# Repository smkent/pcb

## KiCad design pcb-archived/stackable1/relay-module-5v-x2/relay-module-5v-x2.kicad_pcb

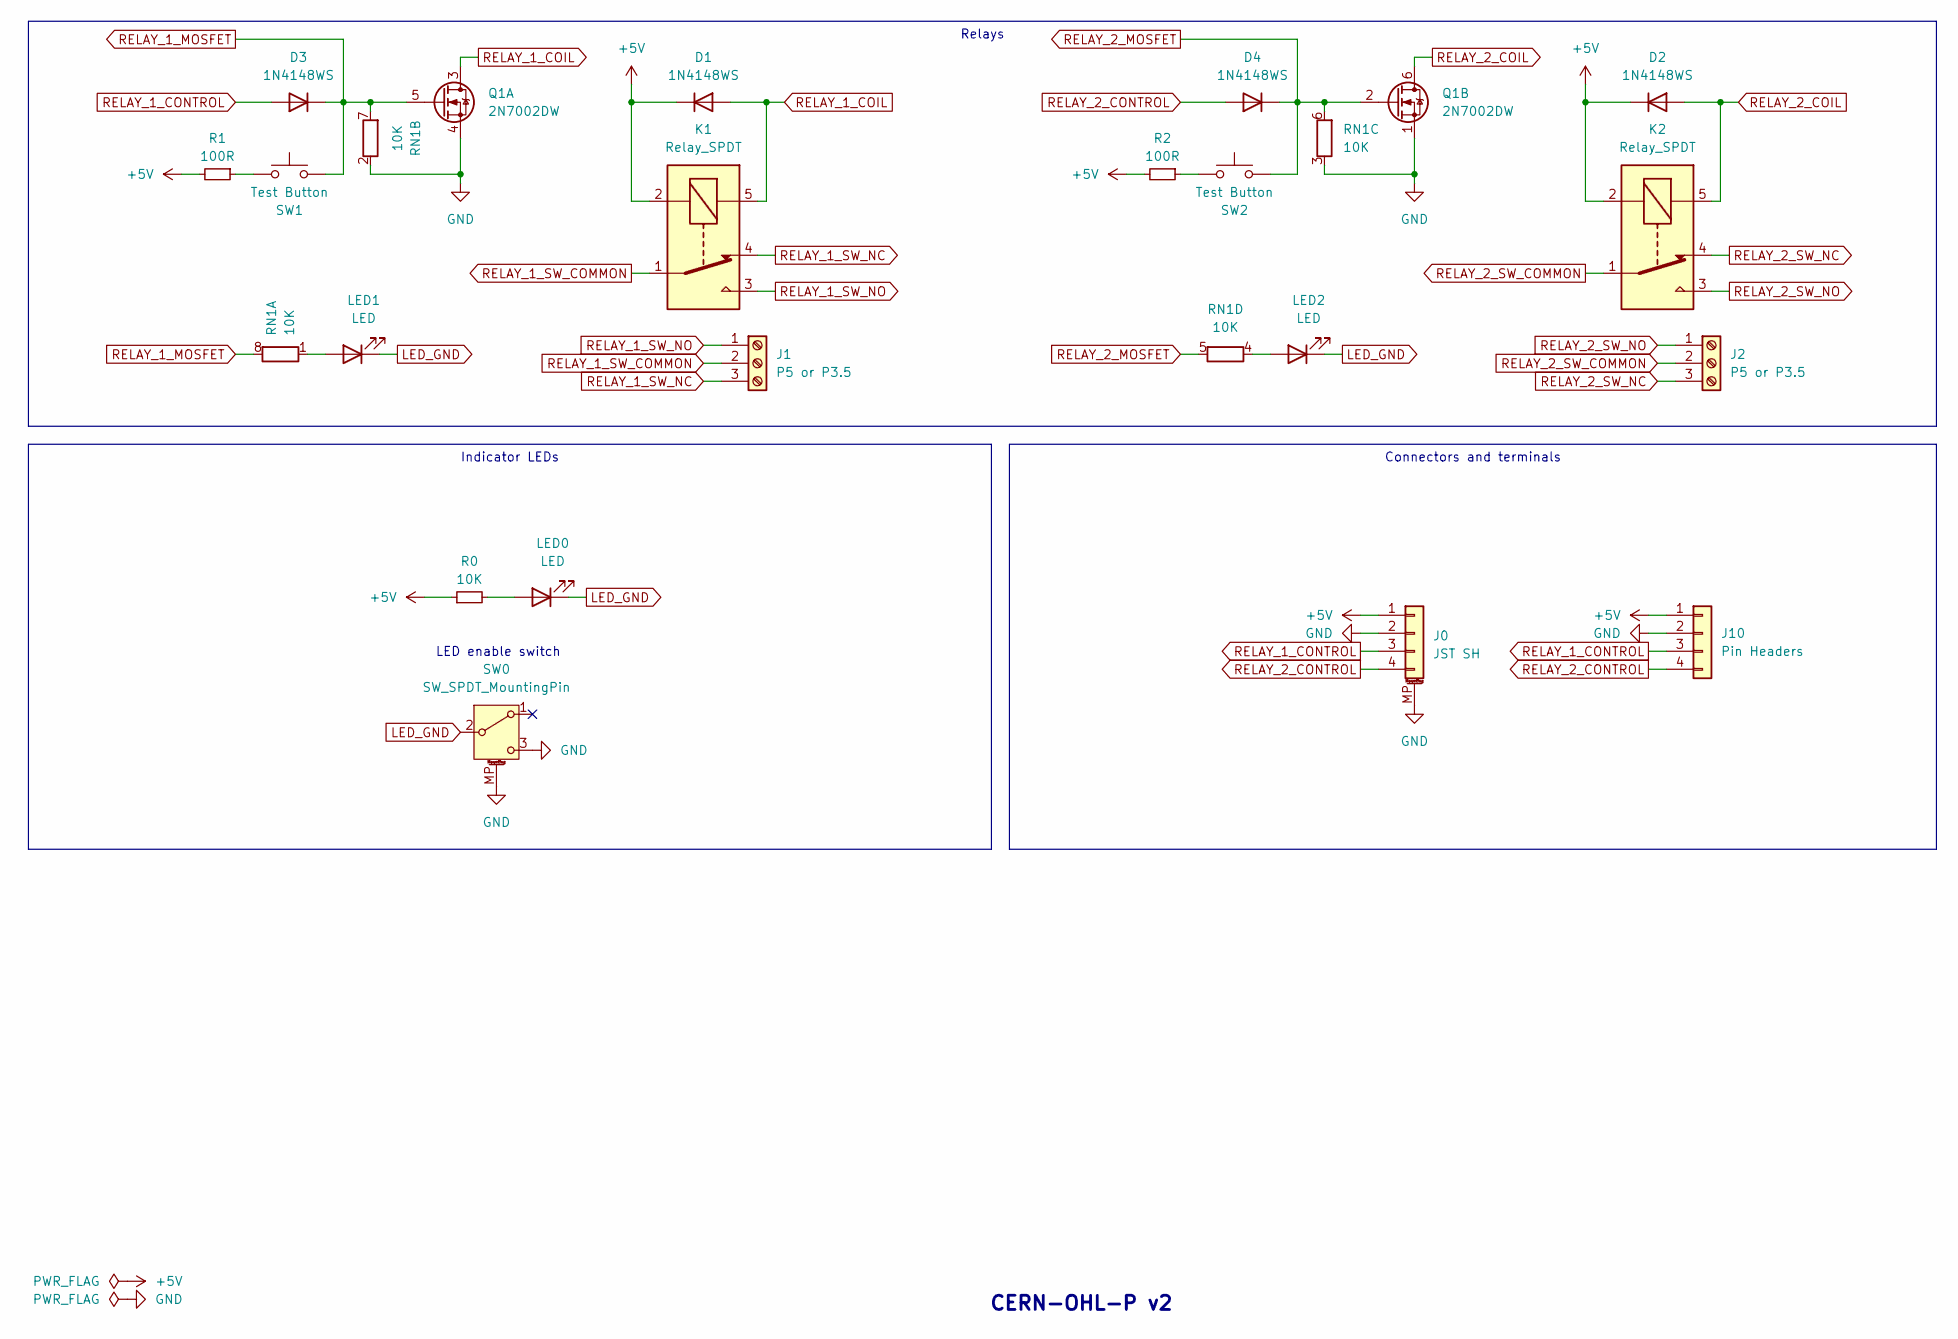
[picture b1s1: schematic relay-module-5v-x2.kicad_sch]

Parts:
D1, D2, D3, D4: 1N4148WS; D_SOD-323_HandSoldering_simple
J0: JST SH; JST_SH_SM04B-SRSS-TB_1x04-1MP_P1.00mm_Horizontal
J1, J2: P5 or P3.5; Conn_Combo_TerminalBlock_P3.5-P5.08_JST-XH_1x03
J10: Pin Headers; PinHeader_1x04_P2.54mm_Vertical_simple_pad2gnd
K1, K2: Relay_SPDT; Relay_SPDT_SANYOU_SRD_Series_Form_C
LED0, LED1, LED2: LED; LED_0805_2012Metric_Pad1.15x1.40mm_HandSolder_simple
Q1: 2N7002DW; SOT-23-6; LCSC Part C5190214
R0: 10K; R_0805_2012Metric_Pad1.20x1.40mm_HandSolder
R1, R2: 100R; R_0805_2012Metric_Pad1.20x1.40mm_HandSolder
RN1: 10K; R_Array_Convex_4x0603
SW0: SW_SPDT_MountingPin; SW-SMD_3P-P1.50_L2.7-W6.6
SW1, SW2: Test Button; SW-SMD_BZCN_TSA002A35XXX

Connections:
+5V: D1.1 (K), D2.1 (K), J0.1, J10.1, K1.2, K2.2, R0.1, R1.2, R2.2
GND: J0.2, J0.MP (MountPin), J10.2, Q1.1 (S), Q1.4 (S), RN1.2 (R2.1), RN1.3 (R3.1), SW0.3 (C), SW0.MP (MountPin)
LED_GND: LED0.1 (K), LED1.1 (K), LED2.1 (K), SW0.2 (B)
unnamed: LED0.2 (A), R0.2
unnamed: LED1.2 (A), RN1.1 (R1.1)
unnamed: LED2.2 (A), RN1.4 (R4.1)
unnamed: R1.1, SW1.2
unnamed: R2.1, SW2.2
RELAY_1_COIL: D1.2 (A), K1.5, Q1.3 (D)
RELAY_1_CONTROL: D3.2 (A), J0.3, J10.3
RELAY_1_MOSFET: D3.1 (K), Q1.5 (G), RN1.7 (R2.2), RN1.8 (R1.2), SW1.1
RELAY_1_SW_COMMON: J1.2, K1.1
RELAY_1_SW_NC: J1.3, K1.4
RELAY_1_SW_NO: J1.1, K1.3
RELAY_2_COIL: D2.2 (A), K2.5, Q1.6 (D)
RELAY_2_CONTROL: D4.2 (A), J0.4, J10.4
RELAY_2_MOSFET: D4.1 (K), Q1.2 (G), RN1.5 (R4.2), RN1.6 (R3.2), SW2.1
RELAY_2_SW_COMMON: J2.2, K2.1
RELAY_2_SW_NC: J2.3, K2.4
RELAY_2_SW_NO: J2.1, K2.3

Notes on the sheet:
Indicator LEDs
Relays
Connectors and terminals
CERN-OHL-P v2
LED enable switch

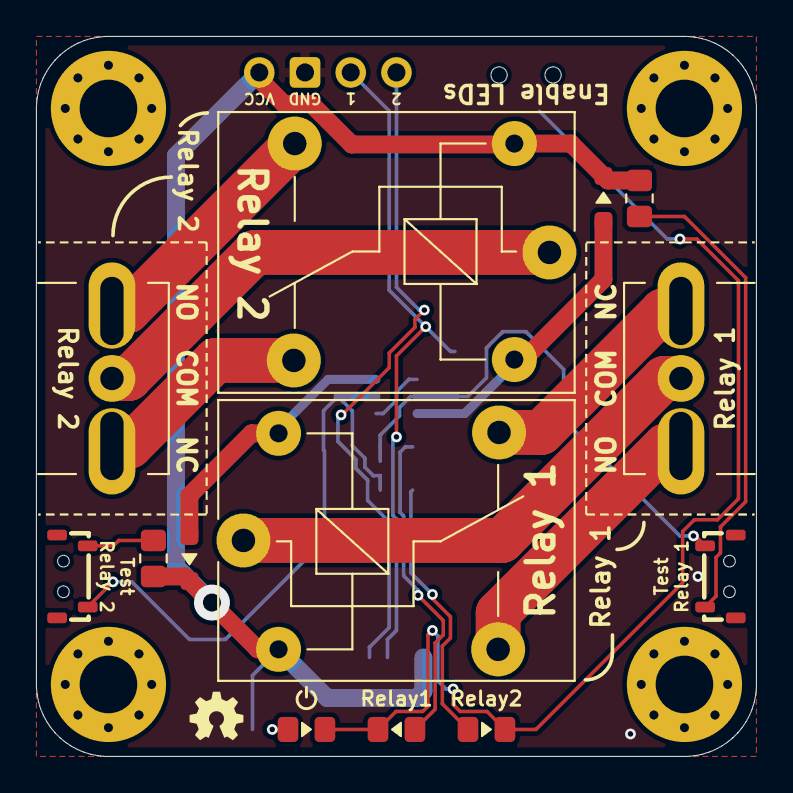
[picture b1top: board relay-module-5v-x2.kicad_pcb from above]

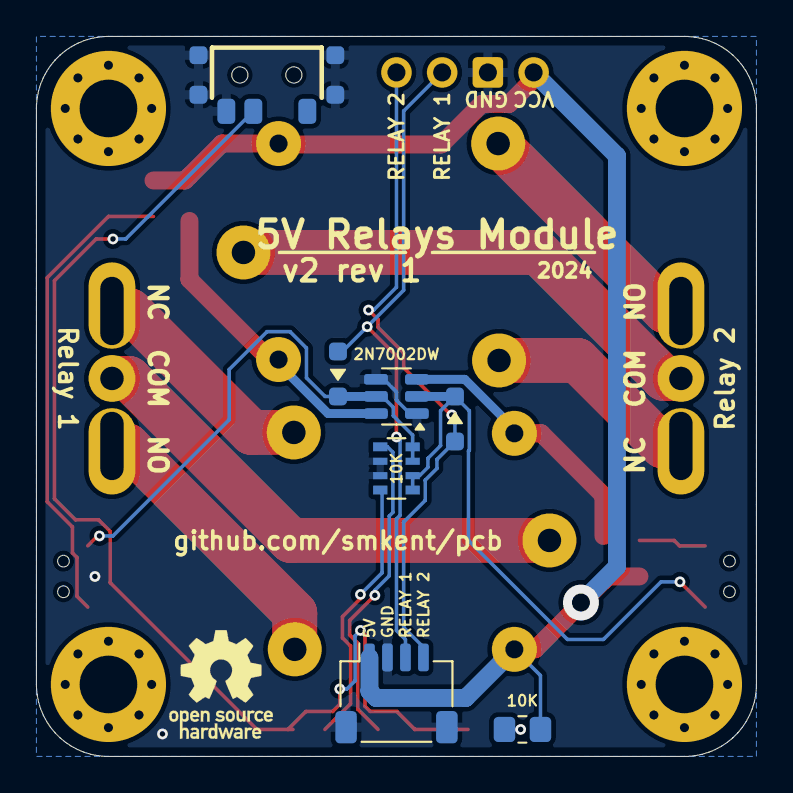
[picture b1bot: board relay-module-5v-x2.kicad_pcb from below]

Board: 2 copper layers, 40.0 x 40.0 mm, 21 parts (7 on the bottom side), 20 nets.

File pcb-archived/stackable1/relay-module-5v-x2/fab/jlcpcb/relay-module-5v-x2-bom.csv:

Comment,Designator,Footprint,LCSC
Pin Headers,J10,custom:PinHeader_1x04_P2.54mm_Vertical_simple_pad2gnd,
Relay_SPDT,"K1,K2",Relay_THT:Relay_SPDT_SANYOU_SRD_Series_Form_C,
100R,"R1,R2",Resistor_SMD:R_0805_2012Metric_Pad1.20x1.40mm_HandSolder,
10K,RN1,Resistor_SMD:R_Array_Convex_4x0603,
LED,"LED0,LED1,LED2",custom:LED_0805_2012Metric_Pad1.15x1.40mm_HandSolder_simple,
1N4148WS,"D1,D2,D3,D4",custom:D_SOD-323_HandSoldering_simple,
10K,R0,Resistor_SMD:R_0805_2012Metric_Pad1.20x1.40mm_HandSolder,
P5 or P3.5,"J1,J2",custom:Conn_Combo_TerminalBlock_P3.5-P5.08_JST-XH_1x03,
2N7002DW,Q1,Package_TO_SOT_SMD:SOT-23-6,C5190214
JST SH,J0,connectors:JST_SH_SM04B-SRSS-TB_1x04-1MP_P1.00mm_Horizontal,
Test Button,"SW1,SW2",lcsc:SW-SMD_BZCN_TSA002A35XXX,
SW_SPDT_MountingPin,SW0,lcsc:SW-SMD_3P-P1.50_L2.7-W6.6,

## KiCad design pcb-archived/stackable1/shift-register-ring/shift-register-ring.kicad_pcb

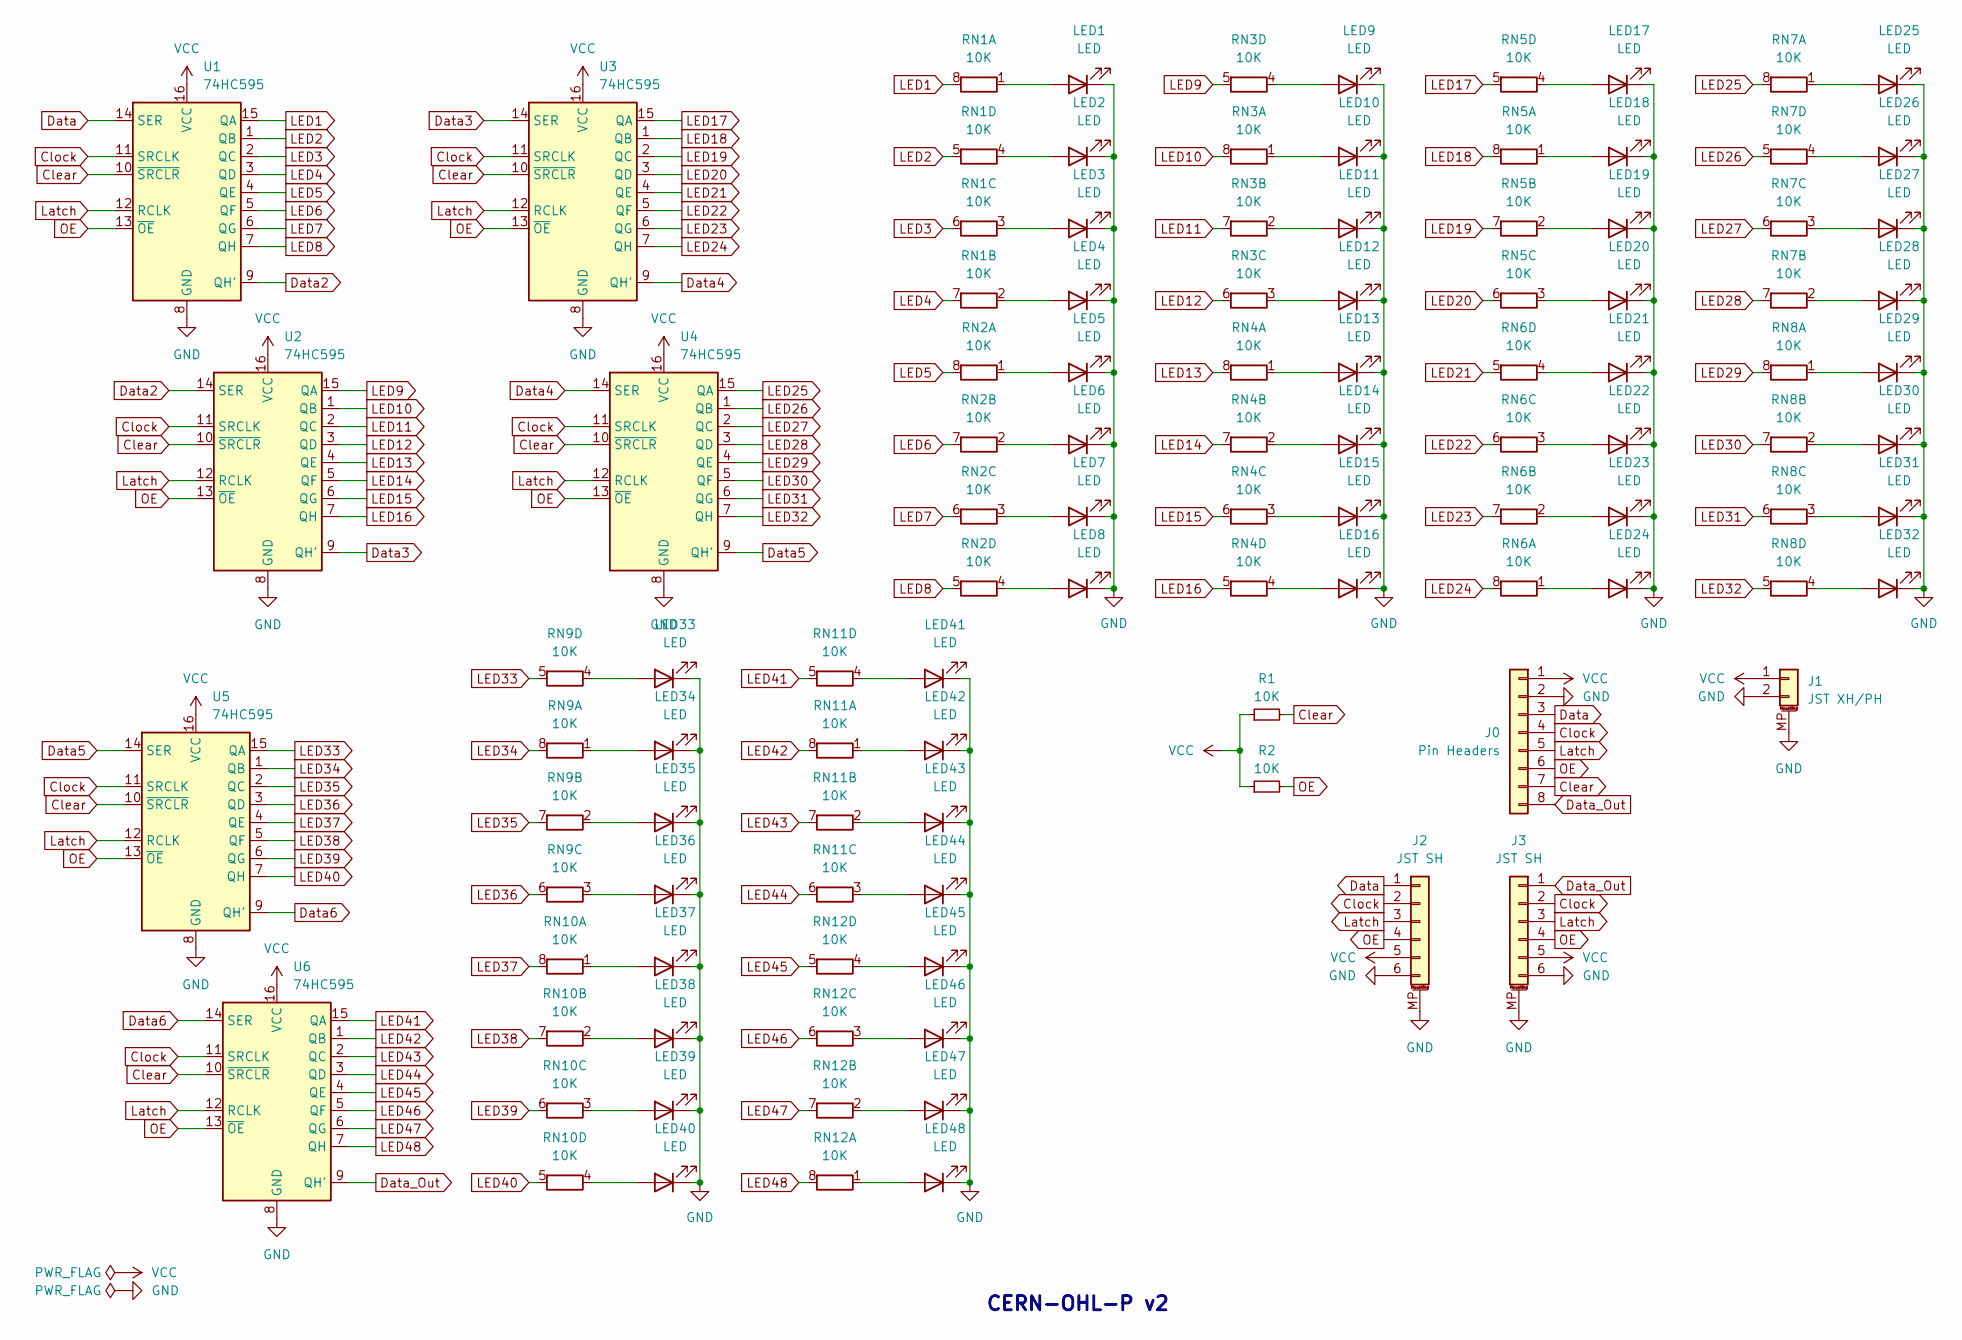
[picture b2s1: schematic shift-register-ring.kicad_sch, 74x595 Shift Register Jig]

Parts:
J0: Pin Headers; PinHeader_1x08_P2.54mm_Vertical_simple_pad2gnd
J1: JST XH/PH; Conn_Combo_JST-1x02-XH_PH-SMD-pad2gnd
J2, J3: JST SH; JST_SH_SM06B-SRSS-TB_1x06-1MP_P1.00mm_Horizontal
LED1, LED2, LED3, LED4, LED5, LED6, LED7, LED8, LED9, LED10, LED11, LED12, LED13, LED14, LED15, LED16, LED17, LED18, LED19, LED20, LED21, LED22, LED23, LED24, LED25, LED26, LED27, LED28, LED29, LED30, LED31, LED32, LED33, LED34, LED35, LED36, LED37, LED38, LED39, LED40, LED41, LED42, LED43, LED44, LED45, LED46, LED47, LED48: LED; LED_0603_1608Metric_Pad1.05x0.95mm_HandSolder_simple
R1, R2: 10K; R_0603_1608Metric_Pad0.98x0.95mm_HandSolder
RN1, RN2, RN3, RN4, RN5, RN6, RN7, RN8, RN9, RN10, RN11, RN12: 10K; R_Array_Convex_4x0603
U1, U2, U3, U4, U5, U6: 74HC595; SOIC-16_3.9x9.9mm_P1.27mm

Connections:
Clear: J0.7, R1.2, U1.10 (~SRCLR), U2.10 (~SRCLR), U3.10 (~SRCLR), U4.10 (~SRCLR), U5.10 (~SRCLR), U6.10 (~SRCLR)
Clock: J0.4, J2.2, J3.2, U1.11 (SRCLK), U2.11 (SRCLK), U3.11 (SRCLK), U4.11 (SRCLK), U5.11 (SRCLK), U6.11 (SRCLK)
Data: J0.3, J2.1, U1.14 (SER)
Data2: U1.9 (QH'), U2.14 (SER)
Data3: U2.9 (QH'), U3.14 (SER)
Data4: U3.9 (QH'), U4.14 (SER)
Data5: U4.9 (QH'), U5.14 (SER)
Data6: U5.9 (QH'), U6.14 (SER)
Data_Out: J0.8, J3.1, U6.9 (QH')
GND: J0.2, J1.2, J1.MP (MountPin), J2.6, J2.MP (MountPin), J3.6, J3.MP (MountPin), LED1.1 (K), LED2.1 (K), LED3.1 (K), LED4.1 (K), LED5.1 (K), LED6.1 (K), LED7.1 (K), LED8.1 (K), LED9.1 (K), LED10.1 (K), LED11.1 (K), LED12.1 (K), LED13.1 (K), LED14.1 (K), LED15.1 (K), LED16.1 (K), LED17.1 (K), LED18.1 (K), LED19.1 (K), LED20.1 (K), LED21.1 (K), LED22.1 (K), LED23.1 (K), LED24.1 (K), LED25.1 (K), LED26.1 (K), LED27.1 (K), LED28.1 (K), LED29.1 (K), LED30.1 (K), LED31.1 (K), LED32.1 (K), LED33.1 (K), LED34.1 (K), LED35.1 (K), LED36.1 (K), LED37.1 (K), LED38.1 (K), LED39.1 (K), LED40.1 (K), LED41.1 (K), LED42.1 (K), LED43.1 (K), LED44.1 (K), LED45.1 (K), LED46.1 (K), LED47.1 (K), LED48.1 (K), U1.8 (GND), U2.8 (GND), U3.8 (GND), U4.8 (GND), U5.8 (GND), U6.8 (GND)
LED1: RN1.8 (R1.2), U1.15 (QA)
LED2: RN1.5 (R4.2), U1.1 (QB)
LED3: RN1.6 (R3.2), U1.2 (QC)
LED4: RN1.7 (R2.2), U1.3 (QD)
LED5: RN2.8 (R1.2), U1.4 (QE)
LED6: RN2.7 (R2.2), U1.5 (QF)
LED7: RN2.6 (R3.2), U1.6 (QG)
LED8: RN2.5 (R4.2), U1.7 (QH)
LED9: RN3.5 (R4.2), U2.15 (QA)
LED10: RN3.8 (R1.2), U2.1 (QB)
LED11: RN3.7 (R2.2), U2.2 (QC)
LED12: RN3.6 (R3.2), U2.3 (QD)
LED13: RN4.8 (R1.2), U2.4 (QE)
LED14: RN4.7 (R2.2), U2.5 (QF)
LED15: RN4.6 (R3.2), U2.6 (QG)
LED16: RN4.5 (R4.2), U2.7 (QH)
LED17: RN5.5 (R4.2), U3.15 (QA)
LED18: RN5.8 (R1.2), U3.1 (QB)
LED19: RN5.7 (R2.2), U3.2 (QC)
LED20: RN5.6 (R3.2), U3.3 (QD)
LED21: RN6.5 (R4.2), U3.4 (QE)
LED22: RN6.6 (R3.2), U3.5 (QF)
LED23: RN6.7 (R2.2), U3.6 (QG)
LED24: RN6.8 (R1.2), U3.7 (QH)
LED25: RN7.8 (R1.2), U4.15 (QA)
LED26: RN7.5 (R4.2), U4.1 (QB)
LED27: RN7.6 (R3.2), U4.2 (QC)
LED28: RN7.7 (R2.2), U4.3 (QD)
LED29: RN8.8 (R1.2), U4.4 (QE)
LED30: RN8.7 (R2.2), U4.5 (QF)
LED31: RN8.6 (R3.2), U4.6 (QG)
LED32: RN8.5 (R4.2), U4.7 (QH)
LED33: RN9.5 (R4.2), U5.15 (QA)
LED34: RN9.8 (R1.2), U5.1 (QB)
LED35: RN9.7 (R2.2), U5.2 (QC)
LED36: RN9.6 (R3.2), U5.3 (QD)
LED37: RN10.8 (R1.2), U5.4 (QE)
LED38: RN10.7 (R2.2), U5.5 (QF)
LED39: RN10.6 (R3.2), U5.6 (QG)
LED40: RN10.5 (R4.2), U5.7 (QH)
LED41: RN11.5 (R4.2), U6.15 (QA)
LED42: RN11.8 (R1.2), U6.1 (QB)
LED43: RN11.7 (R2.2), U6.2 (QC)
LED44: RN11.6 (R3.2), U6.3 (QD)
LED45: RN12.5 (R4.2), U6.4 (QE)
LED46: RN12.6 (R3.2), U6.5 (QF)
LED47: RN12.7 (R2.2), U6.6 (QG)
LED48: RN12.8 (R1.2), U6.7 (QH)
Latch: J0.5, J2.3, J3.3, U1.12 (RCLK), U2.12 (RCLK), U3.12 (RCLK), U4.12 (RCLK), U5.12 (RCLK), U6.12 (RCLK)
unnamed: LED1.2 (A), RN1.1 (R1.1)
unnamed: LED2.2 (A), RN1.4 (R4.1)
unnamed: LED3.2 (A), RN1.3 (R3.1)
unnamed: LED4.2 (A), RN1.2 (R2.1)
unnamed: LED5.2 (A), RN2.1 (R1.1)
unnamed: LED6.2 (A), RN2.2 (R2.1)
unnamed: LED7.2 (A), RN2.3 (R3.1)
unnamed: LED8.2 (A), RN2.4 (R4.1)
unnamed: LED9.2 (A), RN3.4 (R4.1)
unnamed: LED10.2 (A), RN3.1 (R1.1)
unnamed: LED11.2 (A), RN3.2 (R2.1)
unnamed: LED12.2 (A), RN3.3 (R3.1)
unnamed: LED13.2 (A), RN4.1 (R1.1)
unnamed: LED14.2 (A), RN4.2 (R2.1)
unnamed: LED15.2 (A), RN4.3 (R3.1)
unnamed: LED16.2 (A), RN4.4 (R4.1)
unnamed: LED17.2 (A), RN5.4 (R4.1)
unnamed: LED18.2 (A), RN5.1 (R1.1)
unnamed: LED19.2 (A), RN5.2 (R2.1)
unnamed: LED20.2 (A), RN5.3 (R3.1)
unnamed: LED21.2 (A), RN6.4 (R4.1)
unnamed: LED22.2 (A), RN6.3 (R3.1)
unnamed: LED23.2 (A), RN6.2 (R2.1)
unnamed: LED24.2 (A), RN6.1 (R1.1)
unnamed: LED25.2 (A), RN7.1 (R1.1)
unnamed: LED26.2 (A), RN7.4 (R4.1)
unnamed: LED27.2 (A), RN7.3 (R3.1)
unnamed: LED28.2 (A), RN7.2 (R2.1)
unnamed: LED29.2 (A), RN8.1 (R1.1)
unnamed: LED30.2 (A), RN8.2 (R2.1)
unnamed: LED31.2 (A), RN8.3 (R3.1)
unnamed: LED32.2 (A), RN8.4 (R4.1)
unnamed: LED33.2 (A), RN9.4 (R4.1)
unnamed: LED34.2 (A), RN9.1 (R1.1)
unnamed: LED35.2 (A), RN9.2 (R2.1)
unnamed: LED36.2 (A), RN9.3 (R3.1)
unnamed: LED37.2 (A), RN10.1 (R1.1)
unnamed: LED38.2 (A), RN10.2 (R2.1)
unnamed: LED39.2 (A), RN10.3 (R3.1)
unnamed: LED40.2 (A), RN10.4 (R4.1)
unnamed: LED41.2 (A), RN11.4 (R4.1)
unnamed: LED42.2 (A), RN11.1 (R1.1)
unnamed: LED43.2 (A), RN11.2 (R2.1)
unnamed: LED44.2 (A), RN11.3 (R3.1)
unnamed: LED45.2 (A), RN12.4 (R4.1)
unnamed: LED46.2 (A), RN12.3 (R3.1)
unnamed: LED47.2 (A), RN12.2 (R2.1)
unnamed: LED48.2 (A), RN12.1 (R1.1)
OE: J0.6, J2.4, J3.4, R2.2, U1.13 (~OE), U2.13 (~OE), U3.13 (~OE), U4.13 (~OE), U5.13 (~OE), U6.13 (~OE)
VCC: J0.1, J1.1, J2.5, J3.5, R1.1, R2.1, U1.16 (VCC), U2.16 (VCC), U3.16 (VCC), U4.16 (VCC), U5.16 (VCC), U6.16 (VCC)

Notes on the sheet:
CERN-OHL-P v2

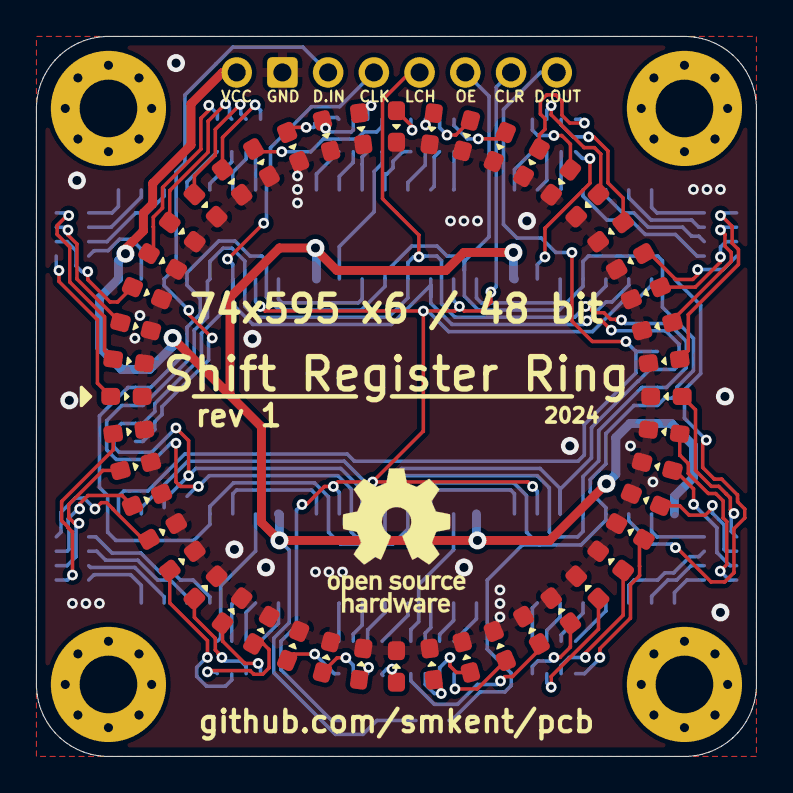
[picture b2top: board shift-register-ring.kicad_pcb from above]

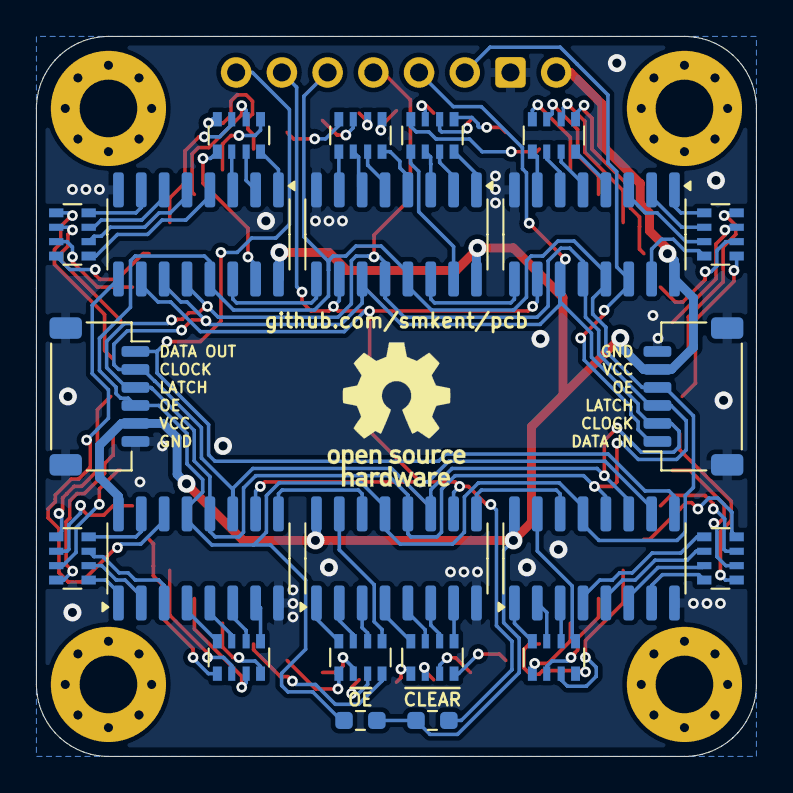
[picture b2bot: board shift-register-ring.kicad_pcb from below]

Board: 2 copper layers, 40.0 x 40.0 mm, 71 parts (23 on the bottom side), 109 nets.

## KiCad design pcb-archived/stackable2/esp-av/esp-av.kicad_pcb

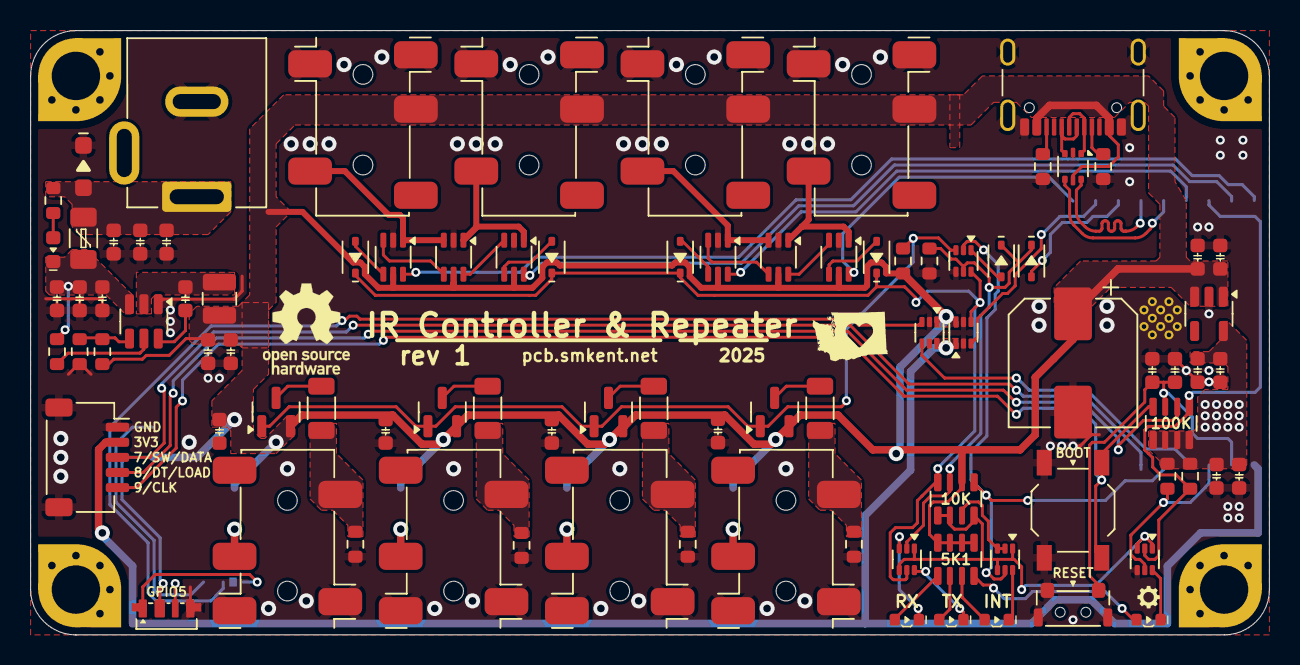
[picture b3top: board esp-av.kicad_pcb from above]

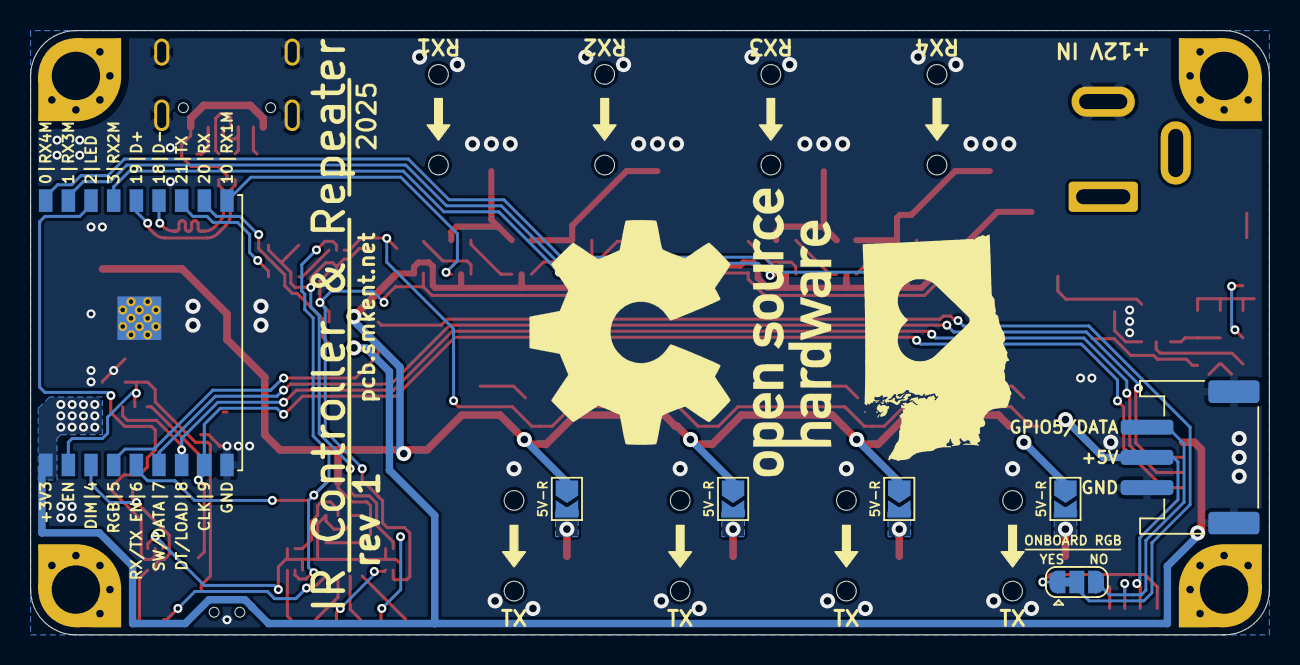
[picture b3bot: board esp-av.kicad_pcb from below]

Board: 2 copper layers, 82.0 x 40.0 mm, 97 parts (7 on the bottom side), 71 nets.

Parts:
C1, C4, C5, C10, C11: 10u; C_0603_1608Metric
C2, C3, C6, C8, C12, C13: 0u1; C_0603_1608Metric
C7: 1u; C_0603_1608Metric
C9: 1000u; CP_Elec_8x10
C14, C15, C16, C17, C18, C19, C20, C21, C22: 22u; C_0603_1608Metric
D0: D_TVS; D_SOD-123F
D1, D2, D3, D4, D5, D6: 1N4148WS; D_SOD-323
F1: 16V 2A; Fuse_1206_3216Metric
J0: DC-005; BarrelJack_DC-005_THT_Horizontal
J1: USB_C_Receptacle_USB2.0_16P; USB_C_Receptacle_GCT_USB4105-xx-A_16P_TopMnt_Horizontal
J2, J3, J4, J5, J6, J7, J8, J9: PJ-327U; Jack_3.5mm_PJ-327U-SMT_Horizontal
J10: JST SH; JST_SH_SM05B-SRSS-TB_1x05-1MP_P1.00mm_Horizontal
J11: STEMMA-Signal; STEMMA-Signal-SMD-horizontal
JP1, JP2, JP3, JP4: Open; SolderJumper-2_P1.3mm_Open_TrianglePad1.0x1.5mm
JP5: 1-2; SolderJumper-3_P1.3mm_Bridged12_RoundedPad1.0x1.5mm
L1: 4u7; L_1008_2520Metric
LED0: Red; LED_0603_1608Metric
LED1, LED2: XL-1606UWC; LED_SideEmitter_1.7x1.1mm
LED3, LED4: XL-1606UBC; LED_SideEmitter_1.7x1.1mm
LED5: SK6812SIDE-A; LED_SK6812SIDE-A_4.0x1.6mm
Q1, Q7, Q8, Q9: PDNM6ET20V05; SOT-563
Q3, Q4, Q5, Q6: AO3401A; SOT-23
R1, R2: 5K1; R_0603_1608Metric
R3, R4, R9: 10K; R_0603_1608Metric
R5, R6, R7, R16, R17, R18: 100K; R_0603_1608Metric
R8: 57K6; R_0603_1608Metric
R10, R11: 2K2; R_0603_1608Metric
R12, R13, R14, R15: 15R; R_1206_3216Metric
RN1: 5K1; R_Array_Convex_4x0603_HandSolder
RN2: 10K; R_Array_Convex_4x0603_HandSolder
RN3: 100K; R_Array_Convex_4x0603_HandSolder
SM1: ESP32-C3-WROOM-02
SW1: Reset; SW_Push_1P1T-MP_NO_4.6x3mm_Horizontal
SW2: Boot; SW_SPST_TL3342
U1: USBLC6-2P6; SOT-666
U2: ME6211C33M5; SOT-23-5
U3: TPS563201; SOT-23-6
U4, U5: NC7WZ14P6X; SOT-363_SC-70-6_HandSolder
U6, U7, U8, U9: SN74LVC1G157DC; SOT-363_SC-70-6_HandSolder
U10, U11: SN74LVC1T45Z6; SOT-563

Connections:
+3V3: C3.1, C4.1, C5.1, C6.1, J10.2, R16.2, R18.2, RN3.5 (R4.2), RN3.6 (R3.2), RN3.7 (R2.2), RN3.8 (R1.2), SM1.1 (3V3), U2.5 (V_{OUT}), U10.1 (VCCA), U11.6 (VCCB)
+5V: C1.1, C2.1, C9.1, C14.1, C15.1, C19.1, C20.1, C21.1, C22.1, J1.A4 (VBUS), J1.A9 (VBUS), J1.B4 (VBUS), J1.B9 (VBUS), J2.R, J3.R, J4.R, J5.R, J11.2 (V+), JP1.1 (A), JP2.1 (A), JP3.1 (A), JP4.1 (A), L1.2, LED5.2 (VDD), Q3.2 (S), Q4.2 (S), Q5.2 (S), Q6.2 (S), R8.2, R11.1, RN1.5 (R4.2), RN1.6 (R3.2), RN1.7 (R2.2), RN1.8 (R1.2), RN2.6 (R3.2), U1.5 (VBUS), U2.1 (V_{IN}), U2.3 (CE), U4.5 (V_{CC}), U5.5 (V_{CC}), U6.5 (V_{CC}), U7.5 (V_{CC}), U8.5 (V_{CC}), U9.5 (V_{CC}), U10.6 (VCCB), U11.1 (VCCA)
+12V: C10.1, C11.1, C12.1, F1.2, LED0.1 (K), R3.1, U3.3 (VIN)
/CC1: J1.A5 (CC1), R2.2
/CC2: J1.B5 (CC2), R1.2
/DC_IN_RAW: C16.1, C17.1, C18.1, D0.2 (A2), F1.1, J0.1, R4.2
/Infrared Transmitter/TX1_5V_J: J6.R, JP1.2 (B)
/Infrared Transmitter/TX1_A_P: Q3.3 (D), R14.1
/Infrared Transmitter/TX2_5V_J: J7.R, JP2.2 (B)
/Infrared Transmitter/TX2_A_P: Q4.3 (D), R12.1
/Infrared Transmitter/TX3_5V_J: J8.R, JP3.2 (B)
/Infrared Transmitter/TX3_A_P: Q5.3 (D), R15.1
/Infrared Transmitter/TX4_5V_J: J9.R, JP4.2 (B)
/Infrared Transmitter/TX4_A_P: Q6.3 (D), R13.1
/PIXEL_DATA: JP5.2 (C), U11.3 (A)
/PIXEL_DIN: JP5.1 (A), LED5.1 (DIN)
/RX_5V_SW: D2.2 (A), Q1.1 (S)
/SW_5V: C13.2, L1.1, U3.2 (SW)
/USB_DM: J1.A7 (D-), J1.B7 (D-), U1.1 (I/O1)
/USB_DP: J1.A6 (D+), J1.B6 (D+), U1.3 (I/O2)
D+: SM1.14 (IO19/USB_D+), U1.4 (I/O2)
D-: SM1.13 (IO18/USB_D-), U1.6 (I/O1)
ESP32_EN: C7.1, C8.1, RN3.3 (R3.1), SM1.2 (EN), SW1.1
FB_5V: R8.1, R9.2, U3.4 (VFB)
GND: C1.2, C2.2, C3.2, C4.2, C5.2, C6.2, C7.2, C8.2, C9.2, C10.2, C11.2, C12.2, C14.2, C15.2, C16.2, C17.2, C18.2, C19.2, C20.2, C21.2, C22.2, D0.1 (A1), J0.2, J1.A1 (GND), J1.A12 (GND), J1.B1 (GND), J1.B12 (GND), J1.S1 (SHIELD), J2.S, J3.S, J4.S, J5.S, J6.S, J7.S, J8.S, J9.S, J10.1, J10.MP (MountPin), J11.1 (Sig), J11.MP, LED5.4 (VSS), Q1.4 (S), Q9.4 (S), R1.1, R2.1, R5.2, R6.2, R7.2, R9.1, R10.2, R17.2, SM1.9 (GND), SM1.19 (GND), SW1.2, SW1.MP (MountPin), SW2.2, U1.2 (GND), U2.2 (V_{SS}), U3.1 (GND), U4.2 (GND), U5.2 (GND), U6.2 (GND), U7.2 (GND), U8.2 (GND), U9.2 (GND), U10.2 (GND), U10.5 (DIR), U11.2 (GND), U11.5 (DIR)
GPIO2: Q9.2 (G), R16.1, RN3.1 (R1.1), SM1.16 (IO2)
IO7/SW/DATA: J10.3, SM1.6 (IO7)
IO8/DT/LOAD: J10.4, RN3.2 (R2.1), SM1.7 (IO8)
IO9/CLK: J10.5, RN3.4 (R4.1), SM1.8 (IO9), SW2.1
LED_EN: Q9.5 (G), R18.1, SM1.3 (IO4)
LED_GND: Q7.1 (S), Q7.4 (S), Q8.1 (S), Q8.4 (S), Q9.1 (S), Q9.3 (D), RN2.1 (R1.1), RN2.2 (R2.1), RN2.4 (R4.1)
unnamed: D3.2 (A), U6.4 (Y)
unnamed: D4.2 (A), U7.4 (Y)
unnamed: D5.2 (A), U8.4 (Y)
unnamed: D6.2 (A), U9.4 (Y)
unnamed: LED0.2 (A), R4.1
unnamed: LED1.2 (A), RN1.4 (R4.1)
unnamed: LED1.1 (K), Q9.6 (D)
unnamed: LED2.2 (A), RN1.3 (R3.1)
unnamed: LED2.1 (K), Q8.6 (D)
unnamed: LED3.2 (A), RN1.1 (R1.1)
unnamed: LED3.1 (K), Q7.3 (D)
unnamed: LED4.2 (A), RN1.2 (R2.1)
unnamed: LED4.1 (K), Q7.6 (D)
unnamed: Q8.2 (G), Q8.3 (D), RN2.3 (R3.1)
unnamed: R3.2, U3.5 (EN)
unnamed: C13.1, U3.6 (VBST)
PIXEL_DATA_3V3: SM1.4 (IO5), U11.4 (B)
PIXEL_DOUT: J11.3 (GND), JP5.3 (B), LED5.3 (DOUT)
RX: D3.1 (K), D4.1 (K), D5.1 (K), D6.1 (K), Q1.6 (D), Q7.5 (G), RN2.8 (R1.2), U10.4 (B)
RX1_5V: J2.T, U4.1 (1A), U6.1 (I1)
RX1_5V_INV: U4.6 (1Y), U6.3 (I0)
RX1_MODE: SM1.10 (IO10), U6.6 (S)
RX2_5V: J3.T, U4.3 (2A), U7.1 (I1)
RX2_5V_INV: U4.4 (2Y), U7.3 (I0)
RX2_MODE: SM1.15 (IO3), U7.6 (S)
RX3_5V: J4.T, U5.1 (1A), U8.1 (I1)
RX3_5V_INV: U5.6 (1Y), U8.3 (I0)
RX3_MODE: SM1.17 (IO1), U8.6 (S)
RX4_5V: J5.T, U5.3 (2A), U9.1 (I1)
RX4_5V_INV: U5.4 (2Y), U9.3 (I0)
RX4_MODE: SM1.18 (IO0), U9.6 (S)
RX_3V3: SM1.11 (IO20/RXD), U10.3 (A)
RX_TX_EN: Q1.2 (G), Q8.5 (G), RN2.5 (R4.2), SM1.5 (IO6)
TX: D1.1 (K), D2.1 (K), Q1.5 (G), Q7.2 (G), R10.1, RN2.7 (R2.2)
TX1_A: J6.T, R5.1, R14.2
TX2_A: J7.T, R6.1, R12.2
TX3_A: J8.T, R7.1, R15.2
TX4_A: J9.T, R13.2, R17.1
TX_3V3: D1.2 (A), SM1.12 (IO21/TXD)
TX_INV: Q1.3 (D), Q3.1 (G), Q4.1 (G), Q5.1 (G), Q6.1 (G), R11.2

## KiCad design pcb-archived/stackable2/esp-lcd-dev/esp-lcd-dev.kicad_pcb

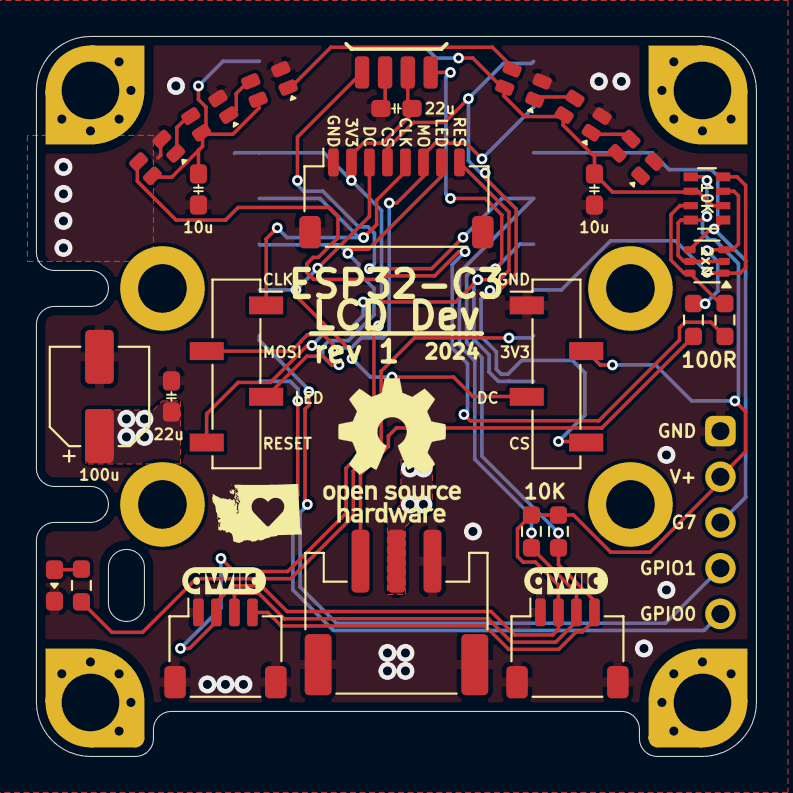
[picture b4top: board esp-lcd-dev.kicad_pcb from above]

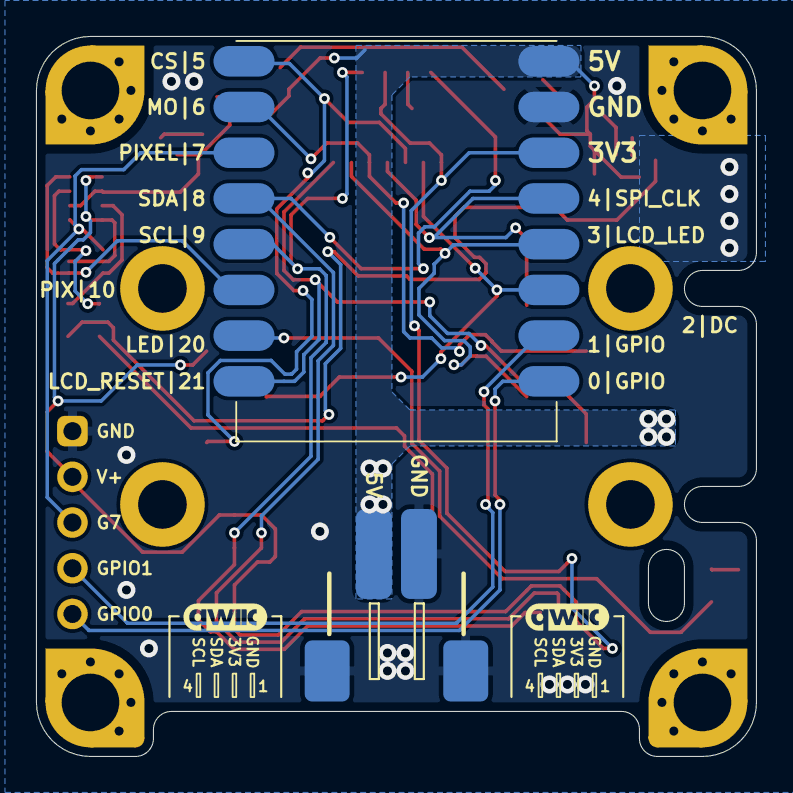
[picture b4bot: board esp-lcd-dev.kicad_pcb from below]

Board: 2 copper layers, 40.0 x 40.0 mm, 29 parts (3 on the bottom side), 26 nets.

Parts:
C1: 100u; CP_Elec_5x5.4
C2, C3: 22u; C_0603_1608Metric_Pad1.08x0.95mm_HandSolder
C6, C7: 10u; C_0603_1608Metric_Pad1.08x0.95mm_HandSolder
J1: JST XH/PH; Conn_Combo_JST-1x02-XH_PH-SMD-pad2gnd
J2, J3: Qwiic; Qwiic-SMD-horizontal-logo-bottom-pinout
J4: STEMMA-Signal; STEMMA-Signal-SMD-horizontal
J5: JST SH; JST_SH_SM08B-SRSS-TB_1x08-1MP_P1.00mm_Horizontal
J6: Pin headers; PinHeader_1x05_P2.54mm_Vertical_simple_pad1gnd
J7: Pin headers; PinSocket_1x04_P2.54mm_Vertical_SMD_Pin1Right
J8: Pin headers; PinSocket_1x04_P2.54mm_Vertical_SMD_Pin1Left
LED1: LED_Small; LED_0603_1608Metric_Pad1.05x0.95mm_HandSolder_simple
LED2, LED3, LED4, LED5, LED6, LED7: WS2812B-2020; LED_WS2812B-2020_PLCC4_2.0x2.0mm_HandSolder
Q1: 2N7002DW; SOT-363_SC-70-6
R1, R4, R5: 10K; R_0603_1608Metric_Pad0.98x0.95mm_HandSolder
R2, R3: 100R; R_0603_1608Metric_Pad0.98x0.95mm_HandSolder
RN2: 10K; R_Array_Convex_4x0603
SM1: ESP32-C3-Super-Mini-Castellated-SMD-only
U1: VEML7700; Sensor_VEML7700-TR

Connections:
+3V3: C3.1, J2.2 (+3V3), J3.2 (+3V3), J5.2, J6.2, J8.2, Q1.2 (G), Q1.5 (G), R4.2, R5.2, RN2.5 (R4.2), RN2.8 (R1.2), SM1.3V3 (+3.3V), U1.2 (VDD)
+5V: C1.1, C2.1, C6.1, C7.1, J1.1, J4.2 (V+), LED2.4 (VDD), LED3.4 (VDD), LED4.4 (VDD), LED5.4 (VDD), LED6.4 (VDD), LED7.4 (VDD), RN2.2 (R2.1), RN2.6 (R3.2), SM1.5V (+5V)
/NP1_5V: Q1.3 (D), R2.2, RN2.3 (R3.1)
/NP2_5V: Q1.6 (D), R3.1, RN2.7 (R2.2)
ENC_CLK: J6.5, SM1.0 (ADC/GPIO0)
ENC_DT: J6.4, SM1.1 (ADC/GPIO1)
GND: C1.2, C2.2, C3.2, C6.2, C7.2, J1.2, J1.MP (MountPin), J2.1 (GND), J2.MP, J3.1 (GND), J3.MP, J4.3 (GND), J4.MP, J5.1, J5.MP (MountPin), J6.1, J8.1, LED1.1 (K), LED2.2 (VSS), LED3.2 (VSS), LED4.2 (VSS), LED5.2 (VSS), LED6.2 (VSS), LED7.2 (VSS), SM1.G (GND), U1.3 (GND)
LCD_BACKLIGHT: J5.7, J7.3, SM1.3 (ADC/GPIO3)
LCD_CS: J5.4, J8.4, SM1.5 (GPIO5/MISO)
LCD_DC: J5.3, J8.3, SM1.2 (ADC/~GPIO2)
LCD_RESET: J5.8, J7.4, SM1.21 (GPIO21/TX)
NEOPIXEL_1_DATA_3V3: J6.3, Q1.4 (S), RN2.1 (R1.1), SM1.7 (GPIO7/SS)
NEOPIXEL_1_DATA_5V: J4.1 (Sig), R2.1
NEOPIXEL_2_DATA_3V3: Q1.1 (S), RN2.4 (R4.1), SM1.10 (GPIO10)
NEOPIXEL_2_DATA_5V: LED2.3 (DIN), R3.2
unnamed: LED1.2 (A), R1.1
unnamed: LED2.1 (DOUT), LED3.3 (DIN)
unnamed: LED3.1 (DOUT), LED4.3 (DIN)
unnamed: LED4.1 (DOUT), LED5.3 (DIN)
unnamed: LED5.1 (DOUT), LED6.3 (DIN)
unnamed: LED6.1 (DOUT), LED7.3 (DIN)
SCL: J2.4 (SCL), J3.4 (SCL), R5.1, SM1.9 (~GPIO9/SCL), U1.1 (SCL)
SDA: J2.3 (SDA), J3.3 (SDA), R4.1, SM1.8 (~GPIO8/SDA), U1.4 (SDA)
SPI_CLK: J5.5, J7.1, SM1.4 (SCK/ADC/GPIO4)
SPI_MOSI: J5.6, J7.2, SM1.6 (GPIO6/MOSI)
STATUS_LED: R1.2, SM1.20 (GPIO20/RX)

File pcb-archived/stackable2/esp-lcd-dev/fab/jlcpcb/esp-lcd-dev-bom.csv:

Comment,Designator,Footprint,LCSC
WS2812B-2020,"LED2,LED3,LED4,LED5,LED6,LED7",lcsc:LED-SMD_4P-L2.0-W2.0-BR-1,
10u,"C6,C7",custom:C_0603_1608Metric_Pad1.08x0.95mm_HandSolder,
100R,"R2,R3",Resistor_SMD:R_0603_1608Metric_Pad0.98x0.95mm_HandSolder,
Qwiic,"J2,J3",connectors:Qwiic-SMD-horizontal-logo-bottom-pinout,
JST XH/PH,J1,custom:Conn_Combo_JST-1x02-XH_PH-SMD-pad2gnd,
10K,"R1,R4,R5",Resistor_SMD:R_0603_1608Metric_Pad0.98x0.95mm_HandSolder,
Pin headers,J8,Connector_PinSocket_2.54mm:PinSocket_1x04_P2.54mm_Vertical_SMD_Pin1Left,
Pin headers,J7,Connector_PinSocket_2.54mm:PinSocket_1x04_P2.54mm_Vertical_SMD_Pin1Right,
STEMMA-Signal,J4,connectors:STEMMA-Signal-SMD-horizontal,
22u,"C2,C3",custom:C_0603_1608Metric_Pad1.08x0.95mm_HandSolder,
100u,C1,Capacitor_SMD:CP_Elec_5x5.4,
VEML7700,U1,lcsc:SENSORS-SMD_VEML7700-TR,
JST SH,J5,connectors:JST_SH_SM08B-SRSS-TB_1x08-1MP_P1.00mm_Horizontal,
~,SM1,modules:ESP32-C3-Super-Mini-Castellated-SMD-only,
Pin headers,J6,custom:PinHeader_1x05_P2.54mm_Vertical_simple_pad1gnd,
2N7002DW,Q1,Package_TO_SOT_SMD:SOT-363_SC-70-6,C5190214
10K,RN2,Resistor_SMD:R_Array_Convex_4x0603,
LED_Small,LED1,custom:LED_0603_1608Metric_Pad1.05x0.95mm_HandSolder_simple,
